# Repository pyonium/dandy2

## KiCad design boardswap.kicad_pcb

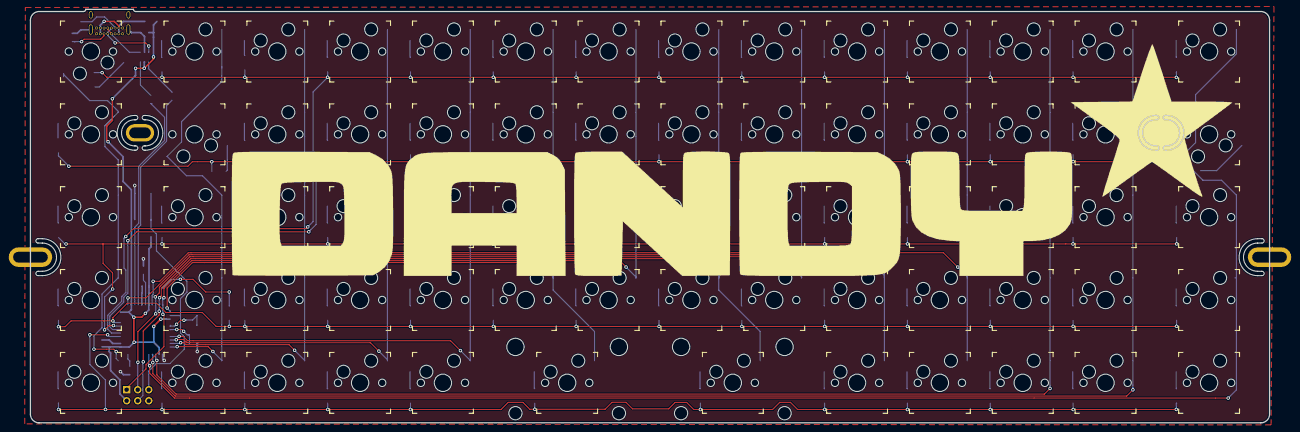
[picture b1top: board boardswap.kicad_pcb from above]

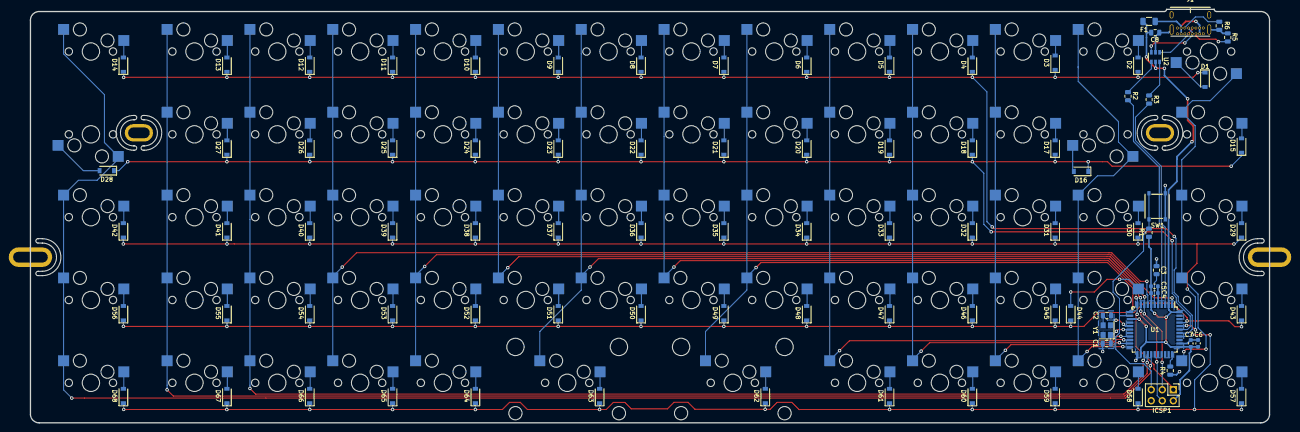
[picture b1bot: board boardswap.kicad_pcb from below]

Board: 2 copper layers, 285.0 x 95.1 mm, 157 parts (89 on the bottom side), 103 nets.

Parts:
C1, C2: 22pF; C_0805_2012Metric
C3: 1uF; C_0805_2012Metric
C4, C5, C6: 0.1uF; C_0603_1608Metric
C7: 10uF; C_0603_1608Metric
C8: 0.1uF; C_0805_2012Metric
D1, D2, D3, D4, D5, D6, D7, D8, D9, D10, D11, D12, D13, D14, D15, D16, D17, D18, D19, D20, D21, D22, D23, D24, D25, D26, D27, D28, D29, D30, D31, D32, D33, D34, D35, D36, D37, D38, D39, D40, D41, D42, D43, D44, D45, D46, D47, D48, D49, D50, D51, D52, D53, D54, D55, D56, D57, D58, D59, D60, D61, D62, D63, D64, D65, D66, D67, D68: D_Small; D_SOD-123
F1: Polyfuse_Small; Fuse_1206_3216Metric
ICSP1: ICSP; PinHeader_2x03_P2.54mm_Vertical
J1: USB_C_Receptacle_USB2.0; USB_C_GCT_USB4085
MX1, MX2, MX3, MX4, MX5, MX6, MX7, MX8, MX9, MX10, MX11, MX12, MX13, MX14, MX15, MX16, MX17, MX18, MX19, MX20, MX21, MX22, MX23, MX24, MX25, MX26, MX27, MX28, MX29, MX30, MX31, MX32, MX33, MX34, MX35, MX36, MX37, MX38, MX39, MX40, MX41, MX42, MX43, MX44, MX45, MX46, MX47, MX48, MX49, MX50, MX51, MX52, MX53, MX54, MX55, MX56, MX57, MX58, MX59, MX60, MX61, MX62, MX63, MX64, MX65, MX66, MX67, MX68: MX-NoLED; Kailh_socket_MX_alt
R1, R4: 10K; R_0805_2012Metric
R2, R3: 22; R_0805_2012Metric
R5, R6: 5.1K; R_0805_2012Metric
SW1: SW_Push; TSButton
U1: ATmega32U4-AU; TQFP-44_10x10mm_P0.8mm
U2: USBLC6-2SC6; SOT-23-6
Y1: 16MHz; Crystal_SMD_3225-4Pin_3.2x2.5mm

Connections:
+5V: C4.1, C5.1, C6.1, C7.1, C8.1, F1.1, ICSP1.2, R1.2, U1.2, U1.7, U1.14, U1.24, U1.34, U1.44, U2.5
COL0: MX1.1, MX15.1, MX29.1, MX43.1, MX57.1
COL1: MX2.1, MX16.1, MX30.1, MX44.1, MX58.1, U1.22
COL2: MX3.1, MX17.1, MX31.1, MX45.1, MX59.1, U1.21
COL3: MX4.1, MX18.1, MX32.1, MX46.1, MX60.1, U1.20
COL4: MX5.1, MX19.1, MX33.1, MX47.1, MX61.1, U1.19
COL5: MX6.1, MX20.1, MX34.1, MX48.1, MX62.1, U1.12
COL6: ICSP1.1, MX7.1, MX21.1, MX35.1, MX49.1, U1.11
COL7: ICSP1.4, MX8.1, MX22.1, MX36.1, MX50.1, MX63.1, U1.10
COL8: ICSP1.3, MX9.1, MX23.1, MX37.1, MX51.1, U1.9
COL9: MX10.1, MX24.1, MX38.1, MX52.1, MX64.1, U1.1
COL10: MX11.1, MX25.1, MX39.1, MX53.1, MX65.1, U1.8
COL11: MX12.1, MX26.1, MX40.1, MX54.1, MX66.1, U1.25
COL12: MX13.1, MX27.1, MX41.1, MX55.1, MX67.1, U1.26
COL13: MX14.1, MX28.1, MX42.1, MX56.1, MX68.1, U1.27
D+: R2.2, U2.4
D-: R3.2, U2.6
GND: C1.2, C2.2, C3.2, C4.2, C5.2, C6.2, C7.2, C8.2, ICSP1.6, J1.A1, J1.A12, J1.B1, J1.B12, J1.S1, R4.1, R5.1, R6.1, SW1.1, U1.5, U1.15, U1.23, U1.35, U1.43, U2.2, Y1.2, Y1.4
unnamed: C1.1, U1.17, Y1.1
unnamed: C2.1, U1.16, Y1.3
unnamed: C3.1, U1.6
unnamed: D1.2, MX1.2
unnamed: D2.2, MX2.2
unnamed: D3.2, MX3.2
unnamed: D4.2, MX4.2
unnamed: D5.2, MX5.2
unnamed: D6.2, MX6.2
unnamed: D7.2, MX7.2
unnamed: D8.2, MX8.2
unnamed: D9.2, MX9.2
unnamed: D10.2, MX10.2
unnamed: D11.2, MX11.2
unnamed: D12.2, MX12.2
unnamed: D13.2, MX13.2
unnamed: D14.2, MX14.2
unnamed: D15.2, MX15.2
unnamed: D16.2, MX16.2
unnamed: D17.2, MX17.2
unnamed: D18.2, MX18.2
unnamed: D19.2, MX19.2
unnamed: D20.2, MX20.2
unnamed: D21.2, MX21.2
unnamed: D22.2, MX22.2
unnamed: D23.2, MX23.2
unnamed: D24.2, MX24.2
unnamed: D25.2, MX25.2
unnamed: D26.2, MX26.2
unnamed: D27.2, MX27.2
unnamed: D28.2, MX28.2
unnamed: D29.2, MX29.2
unnamed: D30.2, MX30.2
unnamed: D31.2, MX31.2
unnamed: D32.2, MX32.2
unnamed: D33.2, MX33.2
unnamed: D34.2, MX34.2
unnamed: D35.2, MX35.2
unnamed: D36.2, MX36.2
unnamed: D37.2, MX37.2
unnamed: D38.2, MX38.2
unnamed: D39.2, MX39.2
unnamed: D40.2, MX40.2
unnamed: D41.2, MX41.2
unnamed: D42.2, MX42.2
unnamed: D43.2, MX43.2
unnamed: D44.2, MX44.2
unnamed: D45.2, MX45.2
unnamed: D46.2, MX46.2
unnamed: D47.2, MX47.2
unnamed: D48.2, MX48.2
unnamed: D49.2, MX49.2
unnamed: D50.2, MX50.2
unnamed: D51.2, MX51.2
unnamed: D52.2, MX52.2
unnamed: D53.2, MX53.2
unnamed: D54.2, MX54.2
unnamed: D55.2, MX55.2
unnamed: D56.2, MX56.2
unnamed: D57.2, MX57.2
unnamed: D58.2, MX58.2
unnamed: D59.2, MX59.2
unnamed: D60.2, MX60.2
unnamed: D61.2, MX61.2
unnamed: D62.2, MX62.2
unnamed: D63.2, MX63.2
unnamed: D64.2, MX64.2
unnamed: D65.2, MX65.2
unnamed: D66.2, MX66.2
unnamed: D67.2, MX67.2
unnamed: D68.2, MX68.2
unnamed: J1.A5, R5.2
unnamed: J1.A6, J1.B6, U2.3
unnamed: J1.A7, J1.B7, U2.1
unnamed: J1.B5, R6.2
unnamed: R2.1, U1.4
unnamed: R3.1, U1.3
unnamed: R4.2, U1.33
RESET: ICSP1.5, R1.1, SW1.2, U1.13
ROW0: D1.1, D2.1, D3.1, D4.1, D5.1, D6.1, D7.1, D8.1, D9.1, D10.1, D11.1, D12.1, D13.1, D14.1, U1.38
ROW1: D15.1, D16.1, D17.1, D18.1, D19.1, D20.1, D21.1, D22.1, D23.1, D24.1, D25.1, D26.1, D27.1, D28.1, U1.39
ROW2: D29.1, D30.1, D31.1, D32.1, D33.1, D34.1, D35.1, D36.1, D37.1, D38.1, D39.1, D40.1, D41.1, D42.1, U1.40
ROW3: D43.1, D44.1, D45.1, D46.1, D47.1, D48.1, D49.1, D50.1, D51.1, D52.1, D53.1, D54.1, D55.1, D56.1, U1.41
ROW4: D57.1, D58.1, D59.1, D60.1, D61.1, D62.1, D63.1, D64.1, D65.1, D66.1, D67.1, D68.1, U1.37
VCC: F1.2, J1.A4, J1.A9, J1.B4, J1.B9

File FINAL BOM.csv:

Comment,Designator,Footprint,LCSC
"22pF","C1,C2","Capacitor_SMD:C_0805_2012Metric","C1804"
"1uF","C3","Capacitor_SMD:C_0805_2012Metric","C28323"
"0.1uF","C4,C5,C6","Capacitor_SMD:C_0603_1608Metric","C14663"
"10uF","C7","Capacitor_SMD:C_0603_1608Metric","C19702"
"0.1uF","C8","Capacitor_SMD:C_0805_2012Metric","C49678"
"D_Small","D1,D2,D3,D4,D5,D6,D7,D8,D9,D10,D11,D12,D13,D14,D15,D16,D17,D18,D19,D20,D21,D22,D23,D24,D25,D26,D27,D28,D29,D30,D31,D32,D33,D34,D35,D36,D37,D38,D39,D40,D41,D42,D43,D44,D45,D46,D47,D48,D49,D50,D51,D52,D53,D54,D55,D56,D57,D58,D59,D60,D61,D62,D63,D64,D65,D66,D67,D68","Diode_SMD:D_SOD-123","C81598"
"Polyfuse_Small","F1","Fuse:Fuse_1206_3216Metric","C70068"
"ICSP","ICSP1","Connector_PinHeader_2.54mm:PinHeader_2x03_P2.54mm_Vertical",""
"USB_C_Receptacle_USB2.0","J1","Type-C:USB_C_GCT_USB4085",""
"MX-NoLED","MX1,MX2,MX3,MX4,MX5,MX6,MX7,MX8,MX9,MX10,MX11,MX12,MX13,MX14,MX15,MX16,MX17,MX18,MX19,MX20,MX21,MX22,MX23,MX24,MX25,MX26,MX27,MX28,MX29,MX30,MX31,MX32,MX33,MX34,MX35,MX36,MX37,MX38,MX39,MX40,MX41,MX42,MX43,MX44,MX45,MX46,MX47,MX48,MX49,MX50,MX51,MX52,MX53,MX54,MX55,MX56,MX57,MX58,MX59,MX60,MX61,MX62,MX63,MX64,MX65,MX66,MX67,MX68","switchprint:Kailh_socket_MX_alt",""
"22","R2,R3","Resistor_SMD:R_0805_2012Metric","C17561"
"10K","R1,R4","Resistor_SMD:R_0805_2012Metric","C17414"
"5.1K","R5,R6","Resistor_SMD:R_0805_2012Metric","C27834"
"SW_Push","SW1","pushbutton:TSButton","C318884"
"ATmega32U4-AU","U1","Package_QFP:TQFP-44_10x10mm_P0.8mm","C44854"
"USBLC6-2SC6","U2","Package_TO_SOT_SMD:SOT-23-6","C7519"
"16MHz","Y1","Crystal:Crystal_SMD_3225-4Pin_3.2x2.5mm","C13738"

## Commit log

2020-09-02 removed junk
2020-09-16 final version, might add flex cuts later
